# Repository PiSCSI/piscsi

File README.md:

# What is PiSCSI?

PiSCSI is a virtual SCSI device emulator that runs on a Raspberry Pi through the [PiSCSI hat](https://github.com/PiSCSI/piscsi/wiki/Hardware-Versions).
The software runs in userspace, and can emulate several SCSI devices at one time.
There is a control interface to attach / detach drives during runtime, as well as insert and eject removable media.

This project aims to be compliant with the SCSI specification and usable with any standards compliant SCSI controller (see [compatibility list](https://github.com/PiSCSI/piscsi/wiki/Compatibility)).
A handful of PiSCSI features were written specifically for vintage Macintosh and Atari computers and may depend on non-free device drivers on the host machine.

PiSCSI is a fork of [RaSCSI](https://github.com/RaSCSI/RaSCSI) and maintains compatibility with any RaSCSI hat.

Please check out the full story with much more detail on the [wiki](https://github.com/PiSCSI/piscsi/wiki)!

Browse the generated [PiSCSI command documentation](https://piscsi.github.io/piscsi/).

## How do I contribute?

PiSCSI is using a variant of the Gitflow Workflow. A quick overview:

- The *main* branch should always reflect the contents of the last stable release
- The *develop* branch should contain the latest tested & approved updates. Pull requests should be used to merge changes into develop.
- The rest of the feature branches are for developing new features
- A tag will be created for each "release". The releases will be named \<year\>.\<month\>.\<release number\> where the release number is incremented for each subsequent release tagged in the same calendar month. The first release of the month of January 2021 is called "21.01.01", the second one in the same month "21.01.02" and so on.

Note that the leading zeroes in the month and release number are used only in the git tags. The equivalent version number in the software is 21.1.1, 21.1.2, etc.

When you are ready to contribute code to PiSCSI, follow the [GitHub Forking and Pull Request workflow](https://docs.github.com/en/get-started/exploring-projects-on-github/contributing-to-a-project) to create your own fork where you can make changes, and then contribute it back to the project. Please remember to always make Pull Requests against the *develop* branch.

If you want to add a new translation, or improve upon an existing one, please follow the [Web Interface localization instructions](go/piscsi-web/README.md#updating-localizations). Once the translation is complete, please use the same workflow as above to contribute it to the project.

## GitHub Sponsors

Thank you to all of the GitHub sponsors who support the development community!

Extra special thank you to the Gold level sponsors!

- [@mikelord68](https://github.com/mikelord68)
- [@SamplerSpa-dev](https://github.com/SamplerSpa-de)

Special thank you to the Silver level sponsors!

- [@stinkerton18](https://github.com/stinkerton18)
- [@hsiboy](https://github.com/hsiboy)
- [@pendleton115](https://github.com/pendleton115)
- [@Teufelhunden-0311](https://github.com/Teufelhunden-0311)
- Private sponsor ;]

Thank you to Lin van der Slikke for the red panda logo design!

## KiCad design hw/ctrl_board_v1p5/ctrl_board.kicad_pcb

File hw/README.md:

# Where's the hardware?

The hardware design files have been moved to a separate repository at:
https://github.com/PiSCSI/piscsi-hw

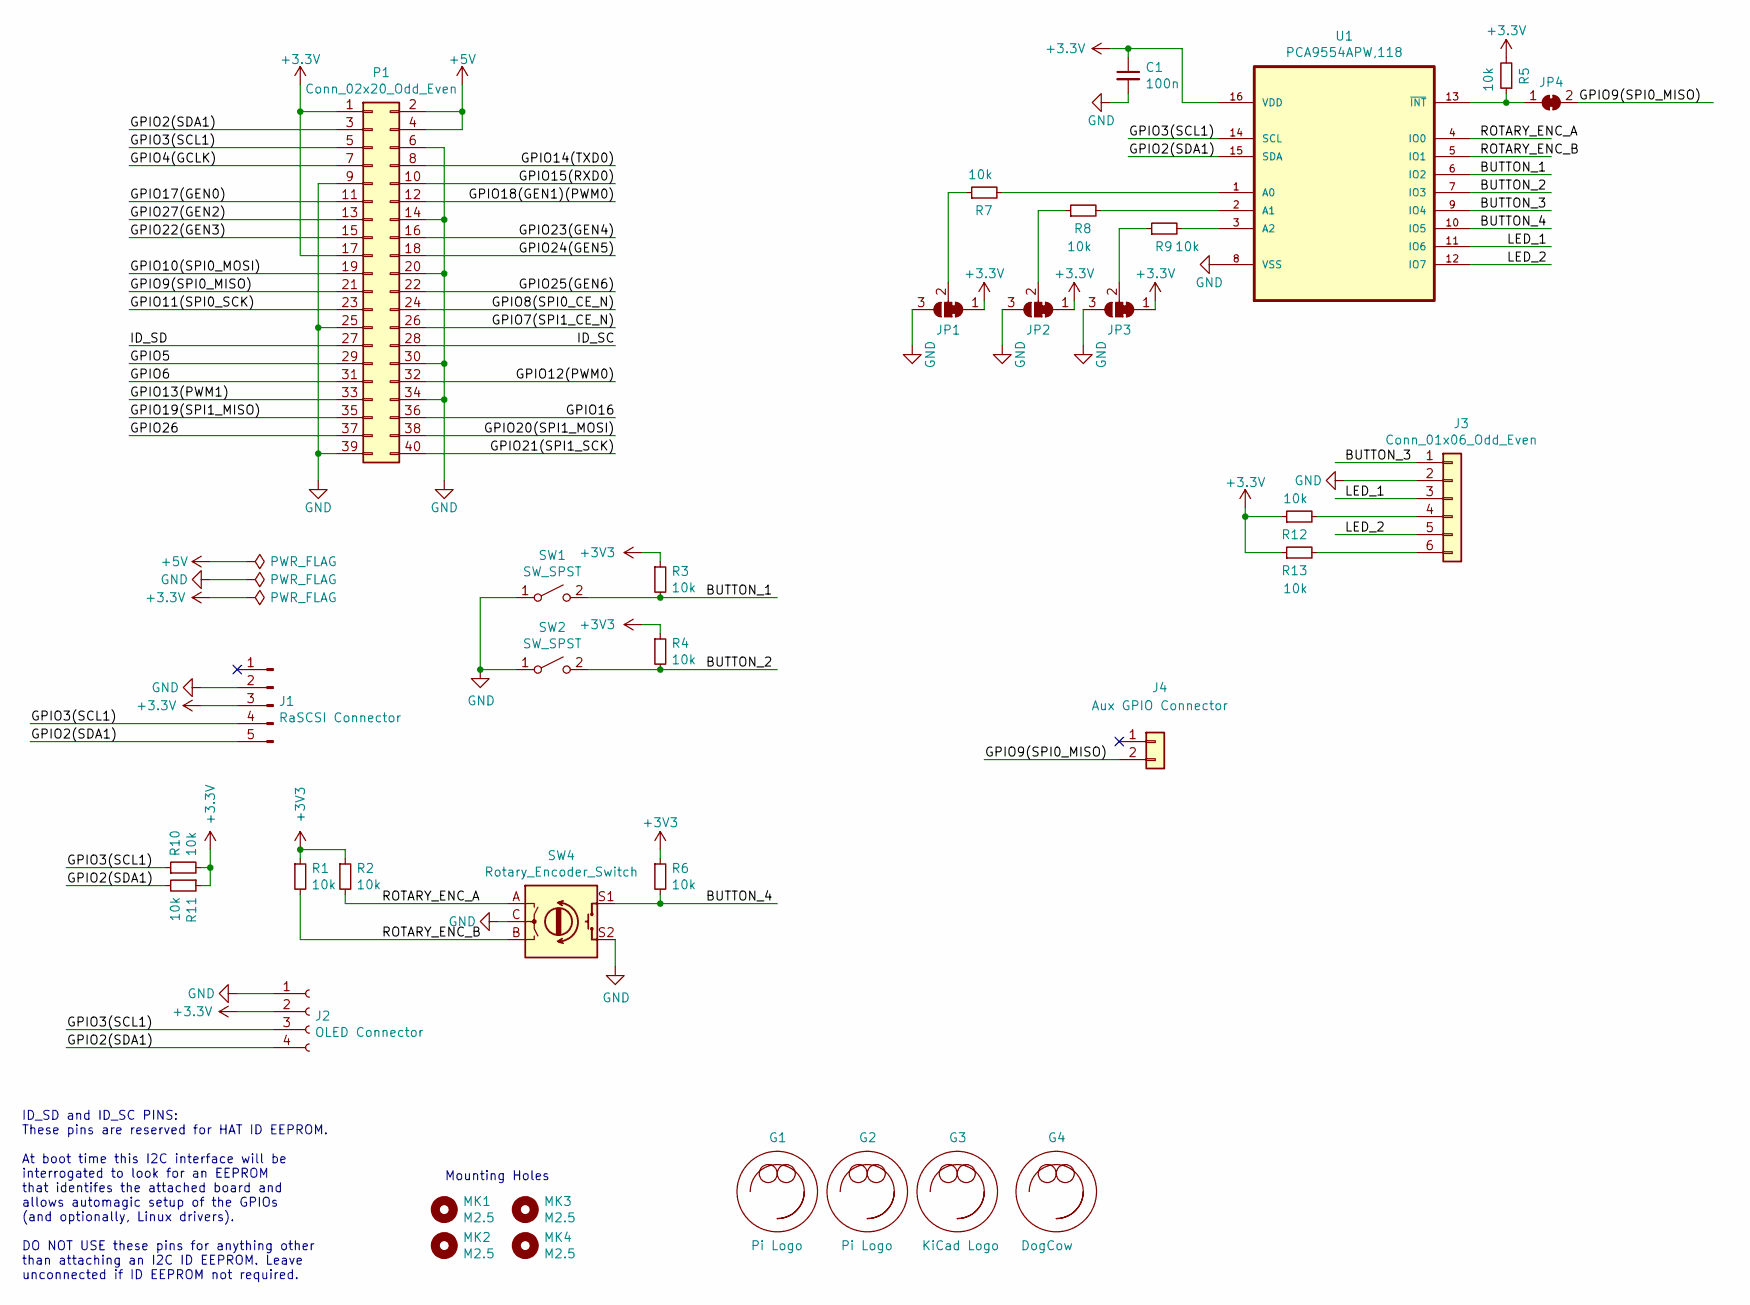
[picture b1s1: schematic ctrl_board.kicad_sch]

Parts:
C1: 100n; C_0805_2012Metric; LCSC C49678
G1, G2: Pi Logo; pi_logo
G3: KiCad Logo; KiCad-Logo2_5mm_SilkScreen
G4: DogCow; dogcow
J1: RaSCSI Connector; PinHeader_1x05_P2.54mm_Vertical
J2: OLED Connector; 0.9_and_1.3_in_OLED_Footprint
J3: Conn_01x06_Odd_Even; PinHeader_1x06_P2.54mm_Vertical
J4: Aux GPIO Connector; PinHeader_1x02_P2.54mm_Vertical
JP1, JP2, JP3: SolderJumper_3_Bridged12; SolderJumper-3_P1.3mm_Bridged12_RoundedPad1.0x1.5mm
JP4: SolderJumper_2_Open; SolderJumper-2_P1.3mm_Bridged_RoundedPad1.0x1.5mm
MK1, MK2, MK3, MK4: M2.5; MountingHole_2.7mm_M2.5
P1: Conn_02x20_Odd_Even; PinSocket_2x20_P2.54mm_Vertical
R1, R2, R3, R4, R5, R6, R7, R8, R9, R10, R11, R12, R13: 10k; R_0805_2012Metric; LCSC C17414
SW1, SW2: SW_SPST; SW_PUSH_6mm_H5mm; LCSC C110153
SW4: Rotary_Encoder_Switch; RotaryEncoder_Alps_EC11E-Switch_Vertical_H20mm
U1: PCA9554APW,118; TSSOP-16_4.4x5mm_P0.65mm; MPN PCA9554APW,118

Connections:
+5V: P1.2, P1.4
/BUTTON_1: R3.2, SW1.2 (B), U1.6 (IO2)
/BUTTON_2: R4.2, SW2.2 (B), U1.7 (IO3)
/BUTTON_3: J3.1, U1.9 (IO4)
/BUTTON_4: R6.2, SW4.S1, U1.10 (IO5)
/GPIO2(SDA1): J1.5, J2.4, P1.3, R11.2, U1.15 (SDA)
/GPIO3(SCL1): J1.4, J2.3, P1.5, R10.1, U1.14 (SCL)
/GPIO4(GCLK): P1.7
/GPIO5: P1.29
/GPIO6: P1.31
/GPIO7(SPI1_CE_N): P1.26
/GPIO8(SPI0_CE_N): P1.24
/GPIO9(SPI0_MISO): J4.2, JP4.2 (B), P1.21
/GPIO10(SPI0_MOSI): P1.19
/GPIO11(SPI0_SCK): P1.23
/GPIO12(PWM0): P1.32
/GPIO13(PWM1): P1.33
/GPIO14(TXD0): P1.8
/GPIO15(RXD0): P1.10
/GPIO16: P1.36
/GPIO17(GEN0): P1.11
/GPIO18(GEN1)(PWM0): P1.12
/GPIO19(SPI1_MISO): P1.35
/GPIO20(SPI1_MOSI): P1.38
/GPIO21(SPI1_SCK): P1.40
/GPIO22(GEN3): P1.15
/GPIO23(GEN4): P1.16
/GPIO24(GEN5): P1.18
/GPIO25(GEN6): P1.22
/GPIO26: P1.37
/GPIO27(GEN2): P1.13
/ID_SC: P1.28
/ID_SD: P1.27
/LED_1: J3.3, U1.11 (IO6)
/LED_2: J3.5, U1.12 (IO7)
/ROTARY_ENC_A: R2.2, SW4.A, U1.4 (IO0)
/ROTARY_ENC_B: R1.2, SW4.B, U1.5 (IO1)
GND: C1.2, J1.2, J2.1, J3.2, JP1.3 (B), JP2.3 (B), JP3.3 (B), P1.6, P1.9, P1.14, P1.20, P1.25, P1.30, P1.34, P1.39, SW1.1 (A), SW2.1 (A), SW4.C, SW4.S2, U1.8 (VSS)
unnamed: J3.4, R12.2
unnamed: J3.6, R13.2
unnamed: JP1.2 (C), R7.1
unnamed: JP2.2 (C), R8.1
unnamed: JP3.2 (C), R9.1
unnamed: JP4.1 (A), R5.1, U1.13 (~INT)
unnamed: R7.2, U1.1 (A0)
unnamed: R8.2, U1.2 (A1)
unnamed: R9.2, U1.3 (A2)

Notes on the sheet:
ID_SD and ID_SC PINS: These pins are reserved for HAT ID EEPROM. At boot time this I2C interface will be interrogated to look for an EEPROM that identifes the attached board and allows automagic setup of the GPIOs (and optionally, Linux drivers). DO NOT USE these pins for anything other than attach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
Mounting Holes

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
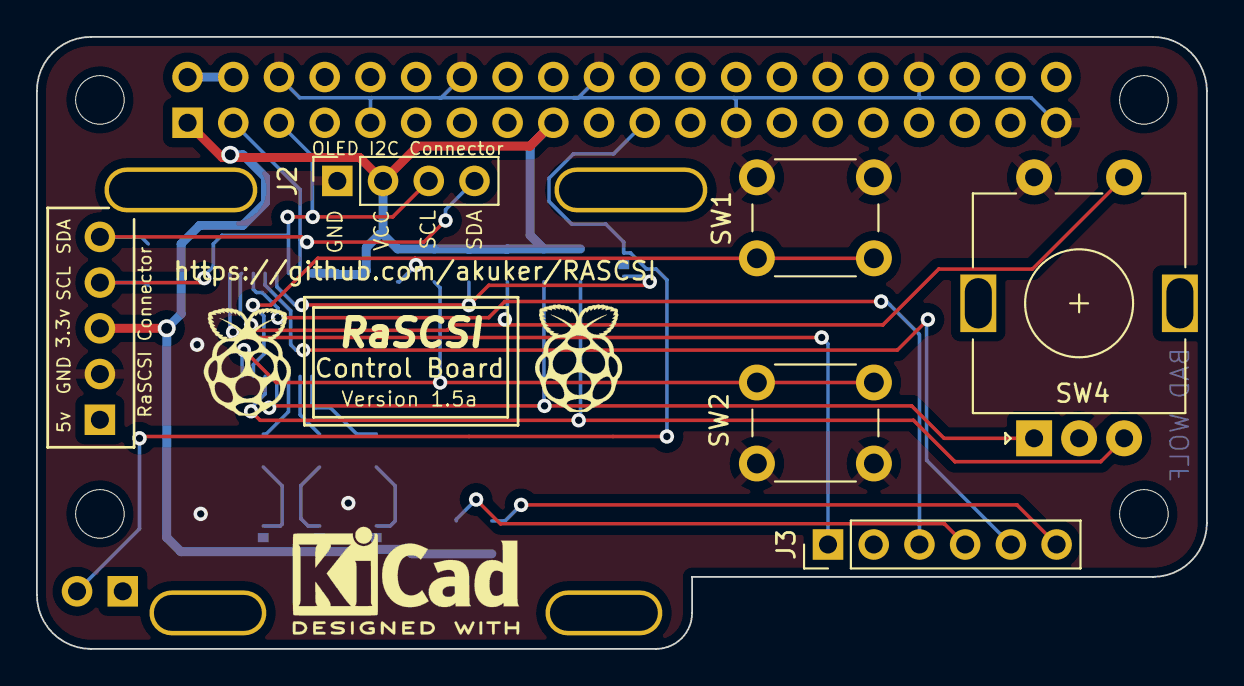
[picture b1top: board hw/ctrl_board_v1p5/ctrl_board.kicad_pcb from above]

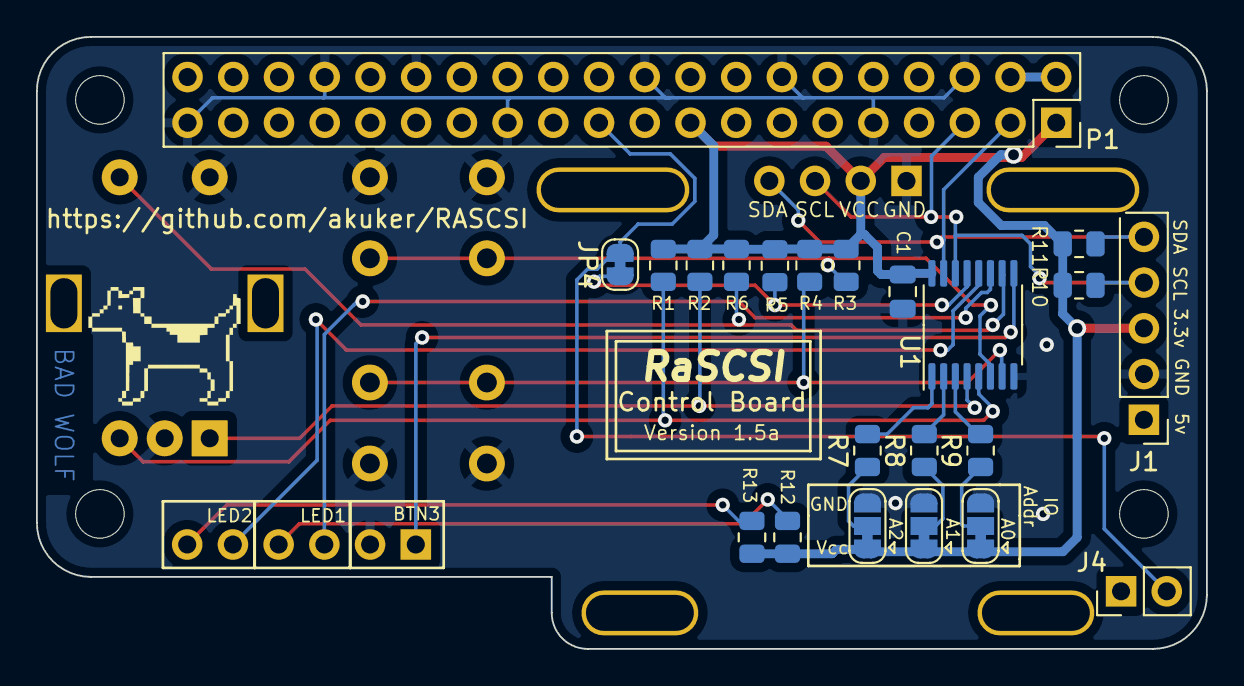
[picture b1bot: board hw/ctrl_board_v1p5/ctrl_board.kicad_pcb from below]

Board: 2 copper layers, 65.0 x 34.0 mm, 35 parts (26 on the bottom side), 23 nets.

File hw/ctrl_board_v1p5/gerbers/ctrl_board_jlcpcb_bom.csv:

Comment,Designator,Footprint,LCSC
"100n","C1","Capacitor_SMD:C_0805_2012Metric","C49678"
"RaSCSI Connector","J1","Connector_PinHeader_2.54mm:PinHeader_1x05_P2.54mm_Vertical",""
"OLED Connector","J2","mousebites:0.9_and_1.3_in_OLED_Footprint",""
"Conn_01x06_Odd_Even","J3","Connector_PinHeader_2.54mm:PinHeader_1x06_P2.54mm_Vertical",""
"Aux GPIO Connector","J4","Connector_PinHeader_2.54mm:PinHeader_1x02_P2.54mm_Vertical",""
"SolderJumper_3_Bridged12","JP1,JP2,JP3","Jumper:SolderJumper-3_P1.3mm_Bridged12_RoundedPad1.0x1.5mm",""
"SolderJumper_2_Open","JP4","Jumper:SolderJumper-2_P1.3mm_Bridged_RoundedPad1.0x1.5mm",""
"M2.5","MK1,MK2,MK3,MK4","MountingHole:MountingHole_2.7mm_M2.5",""
"Conn_02x20_Odd_Even","P1","Connector_PinSocket_2.54mm:PinSocket_2x20_P2.54mm_Vertical",""
"10k","R1,R2,R3,R4,R5,R6,R7,R8,R9,R10,R11,R12,R13","Resistor_SMD:R_0805_2012Metric","C17414"
"SW_SPST","SW1,SW2","Button_Switch_THT:SW_PUSH_6mm_H5mm","C110153"
"Rotary_Encoder_Switch","SW4","Rotary_Encoder:RotaryEncoder_Alps_EC11E-Switch_Vertical_H20mm",""
"PCA9554APW,118","U1","Package_SO:TSSOP-16_4.4x5mm_P0.65mm","C86803"

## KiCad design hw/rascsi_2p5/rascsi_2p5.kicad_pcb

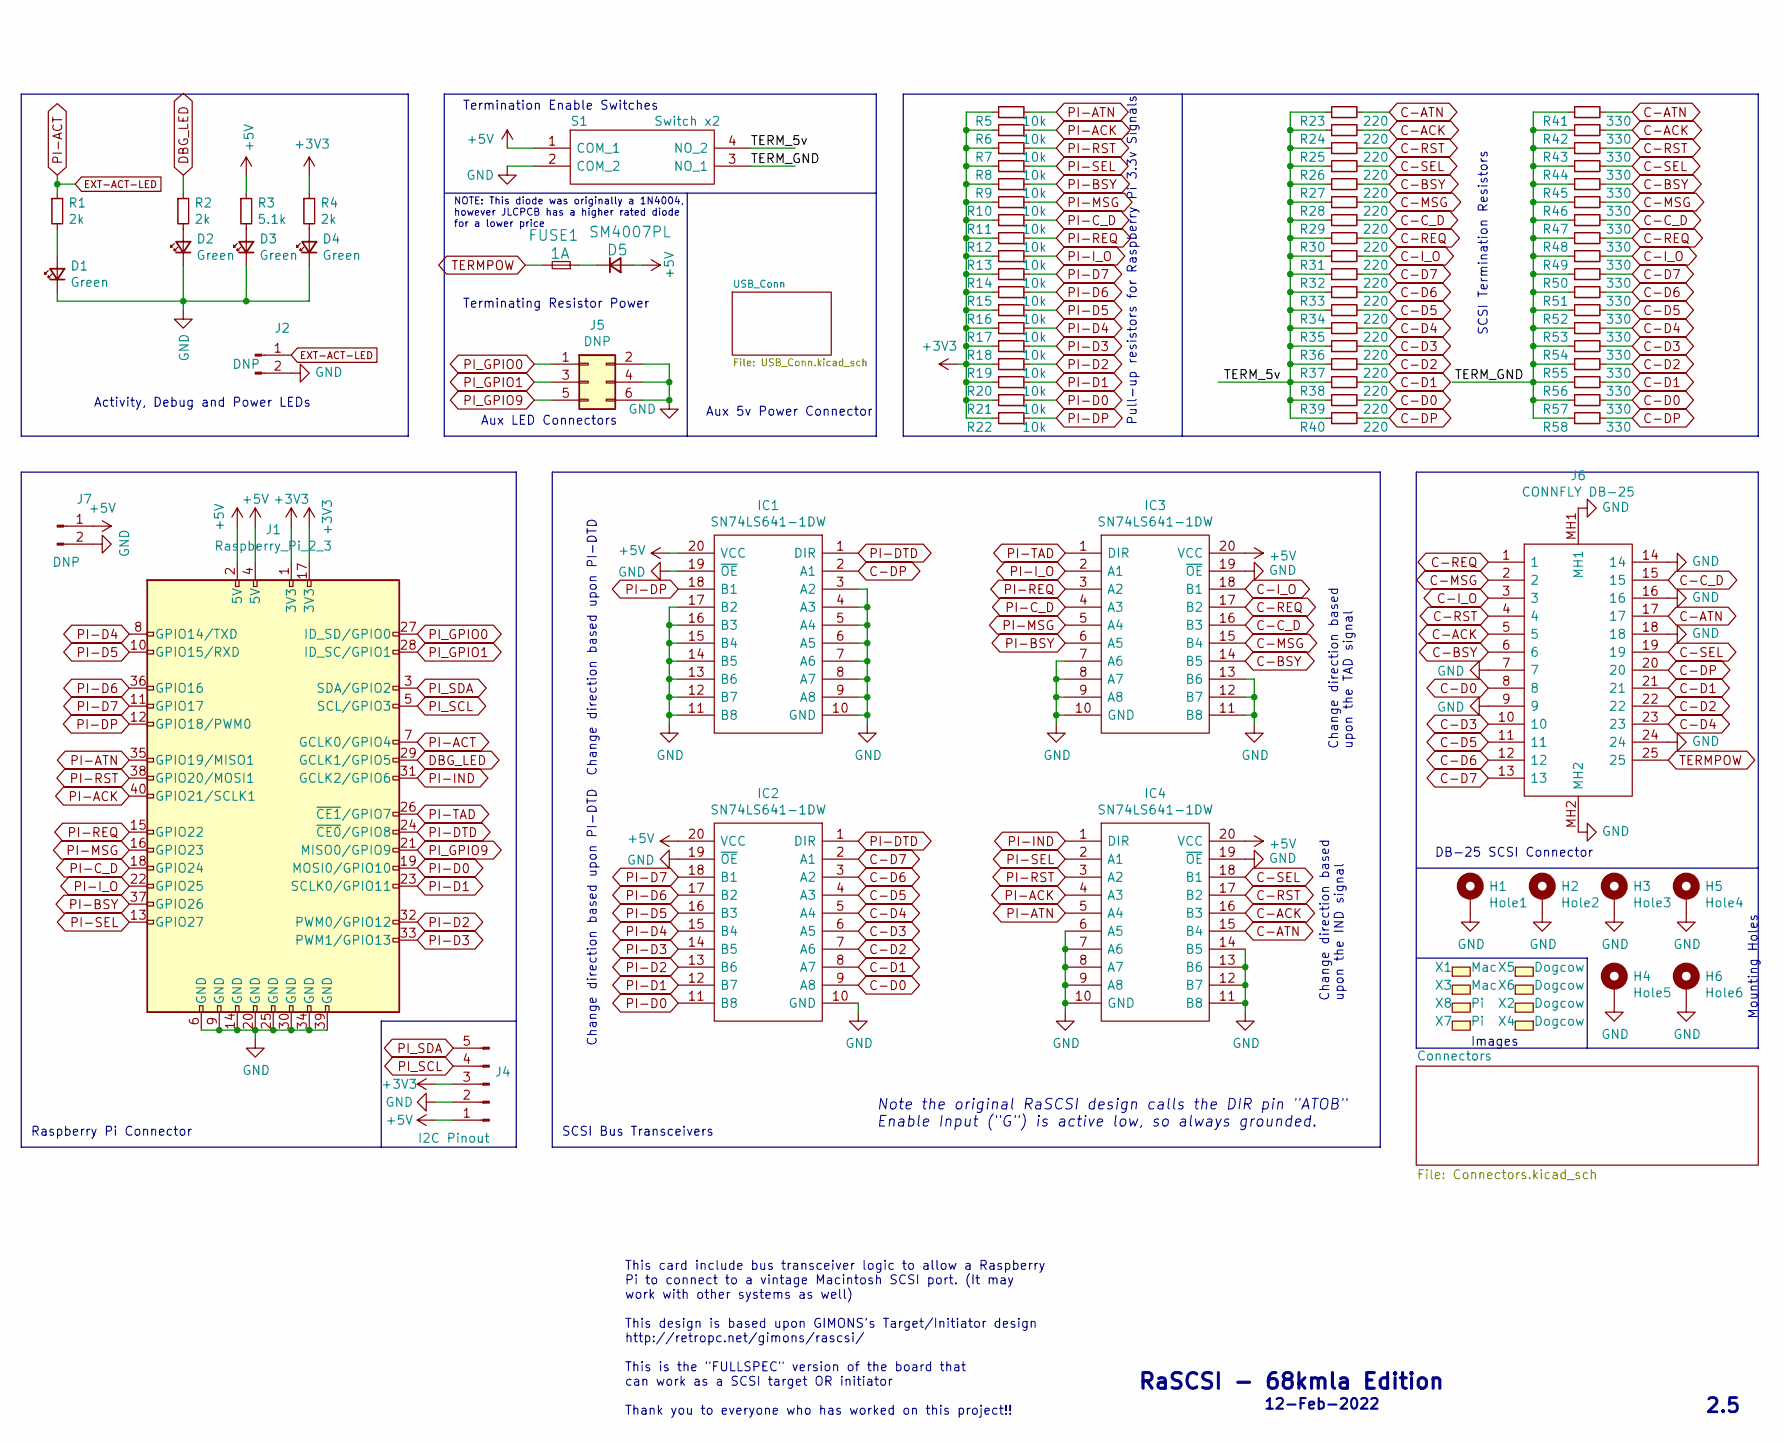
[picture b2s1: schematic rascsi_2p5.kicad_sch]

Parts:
D1, D2, D3, D4: Green; LED_0805_2012Metric; Manufacturer_Part_Number C2297; LCSC C2297
D5: SM4007PL; D_SOD-123F; Manufacturer_Part_Number SM4007PL; LCSC C64898
FUSE1: 1A; Fuse_1206_3216Metric; Manufacturer_Part_Number 12B1100B; LCSC C182974
H1: Hole1; MountingHole_2.7mm_M2.5_Pad_Via; Manufacturer_Part_Number DNP; LCSC DNP
H2: Hole2; MountingHole_2.7mm_M2.5_Pad_Via; Manufacturer_Part_Number DNP; LCSC DNP
H3: Hole3; MountingHole_2.7mm_M2.5_Pad_Via; Manufacturer_Part_Number DNP; LCSC DNP
H4: Hole5; MountingHole_2.7mm_M2.5_Pad_Via; Manufacturer_Part_Number DNP; LCSC DNP
H5: Hole4; MountingHole_2.7mm_M2.5_Pad_Via; Manufacturer_Part_Number DNP; LCSC DNP
H6: Hole6; MountingHole_2.7mm_M2.5_Pad_Via; Manufacturer_Part_Number DNP; LCSC DNP
IC1, IC2, IC3, IC4: SN74LS641-1DW; SOIC127P1030X265-20N; Manufacturer_Part_Number SN74LS641-1DW; LCSC N/A
J1: Raspberry_Pi_2_3; PinSocket_2x20_P2.54mm_Vertical; Manufacturer_Part_Number C50982; LCSC C50982
J2: DNP; PinHeader_1x02_P2.54mm_Horizontal; Manufacturer_Part_Number DNP; LCSC DNP
J4: I2C Pinout; PinSocket_1x05_P2.54mm_Vertical; Manufacturer_Part_Number C50950; LCSC C50950
J5: DNP; PinHeader_2x03_P2.54mm_Vertical; Manufacturer_Part_Number DNP; LCSC DNP
J6: CONNFLY DB-25; L717SDB25PA4CH4F; Manufacturer_Part_Number DS1037-25FNAKT74-0CC; LCSC C77838
J7: DNP; PinHeader_1x02_P2.54mm_Vertical; Manufacturer_Part_Number DNP; LCSC DNP
R1, R2, R4: 2k; R_0402_1005Metric; Manufacturer_Part_Number 0402WGF2001TCE; LCSC C4109
R3: 5.1k; R_0402_1005Metric; Manufacturer_Part_Number 0402WGF5101TCE; LCSC C25905
R5, R6, R7, R8, R9, R10, R11, R12, R13, R14, R15, R16, R17, R18, R19, R20, R21, R22: 10k; R_0402_1005Metric; Manufacturer_Part_Number 0402WGF1002TCE; LCSC C25744
R23, R24, R25, R26, R27, R28, R29, R30, R31, R32, R33, R34, R35, R36, R37, R38, R39, R40: 220; R_0402_1005Metric; Manufacturer_Part_Number 0402WGF2200TCE; LCSC C25091
R41, R42, R43, R44, R45, R46, R47, R48, R49, R50, R51, R52, R53, R54, R55, R56, R57, R58: 330; R_0402_1005Metric; Manufacturer_Part_Number 0402WGF3300TCE; LCSC C25104
S1: Switch x2; SOIC127P812X230-4N; Manufacturer_Part_Number DSHP02TSGET; LCSC C40735
X1, X3: Mac; mac_happy_small; Manufacturer_Part_Number N/A; LCSC N/A
X2, X4, X5, X6: Dogcow; dogcow; Manufacturer_Part_Number N/A; LCSC N/A
X7: Pi; pi_logo; Manufacturer_Part_Number N/A; LCSC N/A
X8: Pi; scsi_logo; Manufacturer_Part_Number N/A; LCSC N/A

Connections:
+3V3: J1.1 (3V3), J1.17 (3V3), J4.3, R4.1, R5.1, R6.1, R7.1, R8.1, R9.1, R10.1, R11.1, R12.1, R13.1, R14.1, R15.1, R16.1, R17.1, R18.1, R19.1, R20.1, R21.1, R22.1
+5V: D5.2 (A), IC1.20 (VCC), IC2.20 (VCC), IC3.20 (VCC), IC4.20 (VCC), J1.2 (5V), J1.4 (5V), J4.1, J7.1, R3.1, S1.1 (COM_1); also elsewhere on the board
/TERM_5v: R23.1, R24.1, R25.1, R26.1, R27.1, R28.1, R29.1, R30.1, R31.1, R32.1, R33.1, R34.1, R35.1, R36.1, R37.1, R38.1, R39.1, R40.1, S1.4 (NO_2)
/TERM_GND: R41.1, R42.1, R43.1, R44.1, R45.1, R46.1, R47.1, R48.1, R49.1, R50.1, R51.1, R52.1, R53.1, R54.1, R55.1, R56.1, R57.1, R58.1, S1.3 (NO_1)
C-ACK: IC4.16 (B3), J6.5, R24.2, R42.2; also elsewhere on the board
C-ATN: IC4.15 (B4), J6.17, R23.2, R41.2; also elsewhere on the board
C-BSY: IC3.14 (B5), J6.6, R27.2, R45.2; also elsewhere on the board
C-C_D: IC3.16 (B3), J6.15, R29.2, R47.2; also elsewhere on the board
C-D0: IC2.9 (A8), J6.8, R39.2, R57.2; also elsewhere on the board
C-D1: IC2.8 (A7), J6.21, R38.2, R56.2; also elsewhere on the board
C-D2: IC2.7 (A6), J6.22, R37.2, R55.2; also elsewhere on the board
C-D3: IC2.6 (A5), J6.10, R36.2, R54.2; also elsewhere on the board
C-D4: IC2.5 (A4), J6.23, R35.2, R53.2; also elsewhere on the board
C-D5: IC2.4 (A3), J6.11, R34.2, R52.2; also elsewhere on the board
C-D6: IC2.3 (A2), J6.12, R33.2, R51.2; also elsewhere on the board
C-D7: IC2.2 (A1), J6.13, R32.2, R50.2; also elsewhere on the board
C-DP: IC1.2 (A1), J6.20, R40.2, R58.2; also elsewhere on the board
C-I_O: IC3.18 (B1), J6.3, R31.2, R49.2; also elsewhere on the board
C-MSG: IC3.15 (B4), J6.2, R28.2, R46.2; also elsewhere on the board
C-REQ: IC3.17 (B2), J6.1, R30.2, R48.2; also elsewhere on the board
C-RST: IC4.17 (B2), J6.4, R25.2, R43.2; also elsewhere on the board
C-SEL: IC4.18 (B1), J6.19, R26.2, R44.2; also elsewhere on the board
DBG_LED: J1.29 (GCLK1/GPIO5), R2.1
GND: D1.1 (K), D2.1 (K), D3.1 (K), D4.1 (K), H1.1, H2.1, H3.1, H4.1, H5.1, H6.1, IC1.3 (A2), IC1.4 (A3), IC1.5 (A4), IC1.6 (A5), IC1.7 (A6), IC1.8 (A7), IC1.9 (A8), IC1.10 (GND), IC1.11 (B8), IC1.12 (B7), IC1.13 (B6), IC1.14 (B5), IC1.15 (B4), IC1.16 (B3), IC1.17 (B2), IC1.19 (~OE), IC2.10 (GND), IC2.19 (~OE), IC3.7 (A6), IC3.8 (A7), IC3.9 (A8), IC3.10 (GND), IC3.11 (B8), IC3.12 (B7), IC3.13 (B6), IC3.19 (~OE), IC4.6 (A5), IC4.7 (A6), IC4.8 (A7), IC4.9 (A8), IC4.10 (GND), IC4.11 (B8), IC4.12 (B7), IC4.13 (B6), IC4.14 (B5), IC4.19 (~OE), J1.6 (GND), J1.9 (GND), J1.14 (GND), J1.20 (GND), J1.25 (GND), J1.30 (GND), J1.34 (GND), J1.39 (GND), J2.2, J4.2, J5.2, J5.4, J5.6, J6.7, J6.9, J6.14, J6.16, J6.18, J6.24, J6.MH1, J6.MH2, J7.2, S1.2 (COM_2); also elsewhere on the board
unnamed: D1.2 (A), R1.2
unnamed: D2.2 (A), R2.2
unnamed: D3.2 (A), R3.2
unnamed: D4.2 (A), R4.2
unnamed: D5.1 (K), FUSE1.1
PB_LED_Pin: J1.7 (GCLK0/GPIO4), J2.1, R1.1; also elsewhere on the board
PI-ACK: IC4.4 (A3), J1.40 (GPIO21/SCLK1), R6.2
PI-ATN: IC4.5 (A4), J1.35 (GPIO19/MISO1), R5.2
PI-BSY: IC3.6 (A5), J1.37 (GPIO26), R9.2
PI-C_D: IC3.4 (A3), J1.18 (GPIO24), R11.2
PI-D0: IC2.11 (B8), J1.19 (MOSI0/GPIO10), R21.2
PI-D1: IC2.12 (B7), J1.23 (SCLK0/GPIO11), R20.2
PI-D2: IC2.13 (B6), J1.32 (PWM0/GPIO12), R19.2
PI-D3: IC2.14 (B5), J1.33 (PWM1/GPIO13), R18.2
PI-D4: IC2.15 (B4), J1.8 (GPIO14/TXD), R17.2
PI-D5: IC2.16 (B3), J1.10 (GPIO15/RXD), R16.2
PI-D6: IC2.17 (B2), J1.36 (GPIO16), R15.2
PI-D7: IC2.18 (B1), J1.11 (GPIO17), R14.2
PI-DP: IC1.18 (B1), J1.12 (GPIO18/PWM0), R22.2
PI-DTD: IC1.1 (DIR), IC2.1 (DIR), J1.24 (~CE0/GPIO8)
PI-IND: IC4.1 (DIR), J1.31 (GCLK2/GPIO6)
PI-I_O: IC3.2 (A1), J1.22 (GPIO25), R13.2
PI-MSG: IC3.5 (A4), J1.16 (GPIO23), R10.2
PI-REQ: IC3.3 (A2), J1.15 (GPIO22), R12.2
PI-RST: IC4.3 (A2), J1.38 (GPIO20/MOSI1), R7.2
PI-SEL: IC4.2 (A1), J1.13 (GPIO27), R8.2
PI-TAD: IC3.1 (DIR), J1.26 (~CE1/GPIO7)
PI_GPIO0: J1.27 (ID_SD/GPIO0), J5.1
PI_GPIO1: J1.28 (ID_SC/GPIO1), J5.3
PI_GPIO9: J1.21 (MISO0/GPIO9), J5.5
PI_SCL: J1.5 (SCL/GPIO3), J4.4
PI_SDA: J1.3 (SDA/GPIO2), J4.5
TERMPOW: FUSE1.2, J6.25; also elsewhere on the board

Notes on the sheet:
Images
RaSCSI - 68kmla Edition
2.5
Raspberry Pi Connector
Change direction based upon the TAD signal
Terminating Resistor Power
Mounting Holes
12-Feb-2022
DB-25 SCSI Connector
SCSI Termination Resistors
Pull-up resistors for Raspberry Pi 3.3v Signals
Change direction based upon the IND signal
NOTE: This diode was originally a 1N4004, however JLCPCB has a higher rated diode for a lower price
Change direction based upon PI-DTD
Note the original RaSCSI design calls the DIR pin "ATOB" Enable Input ("G") is active low, so always grounded.
Activity, Debug and Power LEDs
Termination Enable Switches
This card include bus transceiver logic to allow a Raspberry Pi to connect to a vintage Macintosh SCSI port. (It may work with other systems as well) This design is based upon GIMONS's Target/Initiator design http://retropc.net/gimons/rascsi/ This is the "FULLSPEC" version of the board that can wor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
Aux 5v Power Connector
SCSI Bus Transceivers
Aux LED Connectors

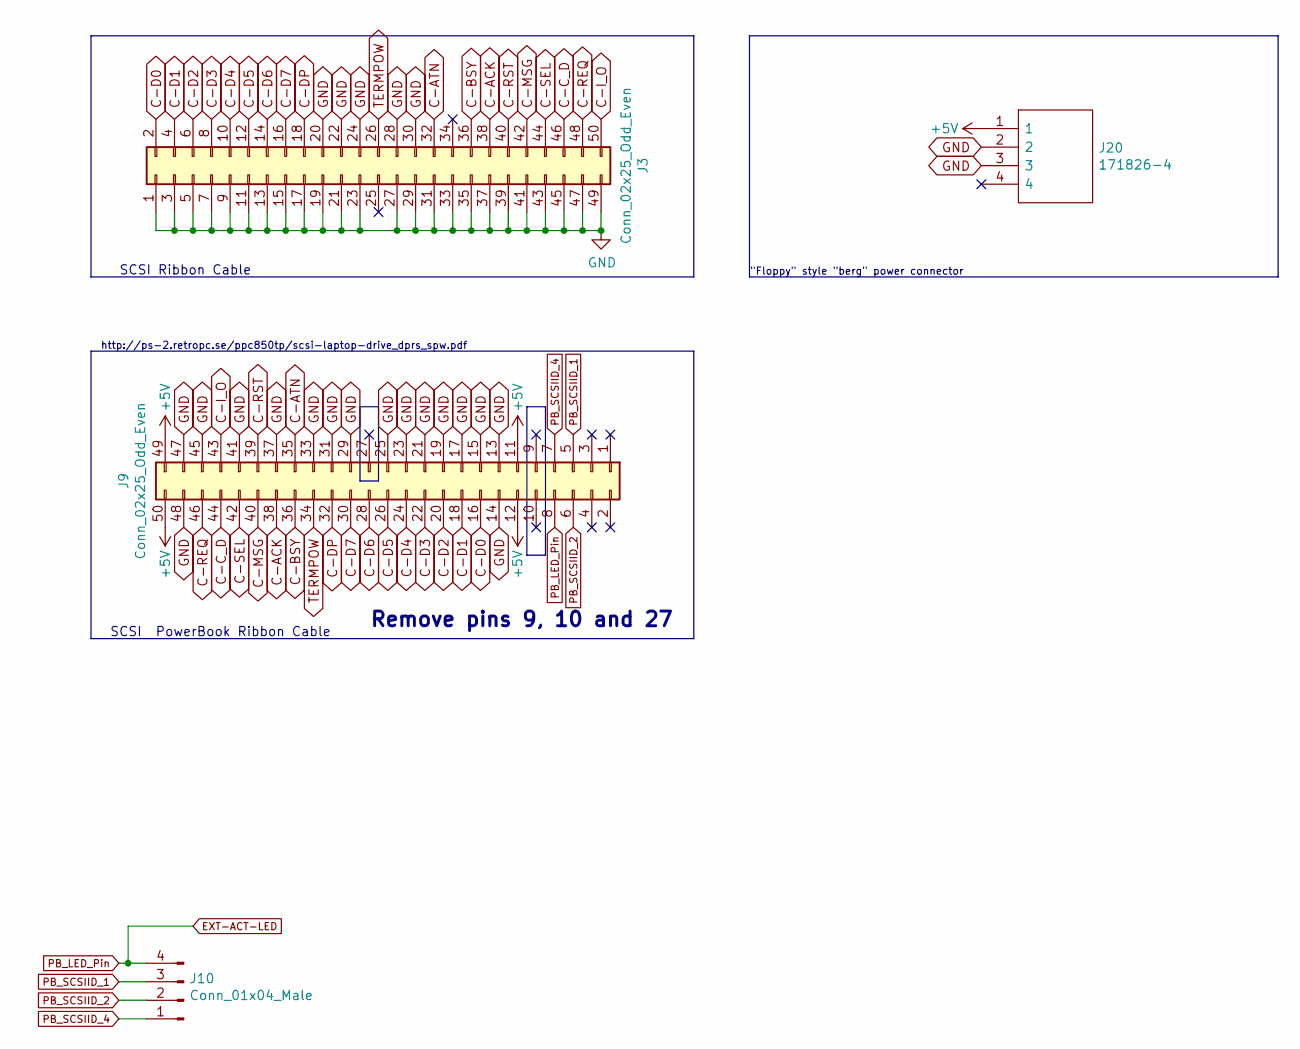
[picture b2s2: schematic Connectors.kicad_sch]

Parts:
J3: Conn_02x25_Odd_Even; PinHeader_2x25_P2.54mm_Vertical; Manufacturer_Part_Number C30006; LCSC C30006
J9: Conn_02x25_Odd_Even; PinHeader_2x25_P2.00mm_Horizontal; Manufacturer_Part_Number C3407; LCSC C3407
J10: Conn_01x04_Male; PinHeader_1x04_P2.00mm_Vertical
J20: 171826-4; SHDRRA4W69P0X250_1X4_1000X1350X670P; Mouser Part Number 571-1718264

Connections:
+5V: J9.11, J9.12, J9.49, J9.50, J20.1; also elsewhere on the board
C-ACK: J3.38, J9.38; also elsewhere on the board
C-ATN: J3.32, J9.35; also elsewhere on the board
C-BSY: J3.36, J9.36; also elsewhere on the board
C-C_D: J3.46, J9.44; also elsewhere on the board
C-D0: J3.2, J9.16; also elsewhere on the board
C-D1: J3.4, J9.18; also elsewhere on the board
C-D2: J3.6, J9.20; also elsewhere on the board
C-D3: J3.8, J9.22; also elsewhere on the board
C-D4: J3.10, J9.24; also elsewhere on the board
C-D5: J3.12, J9.26; also elsewhere on the board
C-D6: J3.14, J9.28; also elsewhere on the board
C-D7: J3.16, J9.30; also elsewhere on the board
C-DP: J3.18, J9.32; also elsewhere on the board
C-I_O: J3.50, J9.43; also elsewhere on the board
C-MSG: J3.42, J9.40; also elsewhere on the board
C-REQ: J3.48, J9.46; also elsewhere on the board
C-RST: J3.40, J9.39; also elsewhere on the board
C-SEL: J3.44, J9.42; also elsewhere on the board
GND: J3.1, J3.3, J3.5, J3.7, J3.9, J3.11, J3.13, J3.15, J3.17, J3.19, J3.20, J3.21, J3.22, J3.23, J3.24, J3.27, J3.28, J3.29, J3.30, J3.31, J3.33, J3.35, J3.37, J3.39, J3.41, J3.43, J3.45, J3.47, J3.49, J9.13, J9.14, J9.15, J9.17, J9.19, J9.21, J9.23, J9.25, J9.29, J9.31, J9.33, J9.37, J9.41, J9.45, J9.47, J9.48, J20.2, J20.3; also elsewhere on the board
PB_LED_Pin: J9.8, J10.4; also elsewhere on the board
PB_SCSIID_1: J9.5, J10.3
PB_SCSIID_2: J9.6, J10.2
PB_SCSIID_4: J9.7, J10.1
TERMPOW: J3.26, J9.34; also elsewhere on the board

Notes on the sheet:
Remove pins 9, 10 and 27
SCSI Ribbon Cable
"Floppy" style "berg" power connector
http://ps-2.retropc.se/ppc850tp/scsi-laptop-drive_dprs_spw.pdf
SCSI PowerBook Ribbon Cable

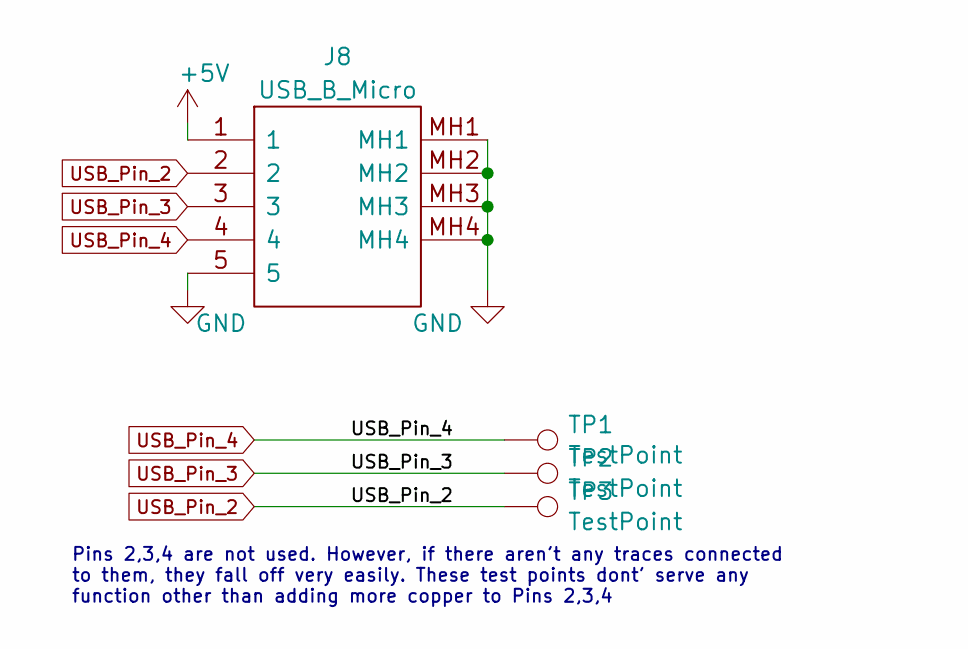
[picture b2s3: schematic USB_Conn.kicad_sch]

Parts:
J8: USB_B_Micro; U254051N4BH806; Manufacturer_Part_Number U254-051N-4BH806; LCSC C319170
TP1, TP2, TP3: TestPoint; TestPoint_Pad_D1.0mm; Manufacturer_Part_Number N/A; LCSC N/A

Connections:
+5V: J8.1; also elsewhere on the board
GND: J8.5, J8.MH1, J8.MH2, J8.MH3, J8.MH4; also elsewhere on the board
USB_Pin_2: J8.2, TP3.1
USB_Pin_3: J8.3, TP2.1
USB_Pin_4: J8.4, TP1.1

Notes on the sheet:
Pins 2,3,4 are not used. However, if there aren't any traces connected to them, they fall off very easily. These test points dont' serve any function other than adding more copper to Pins 2,3,4

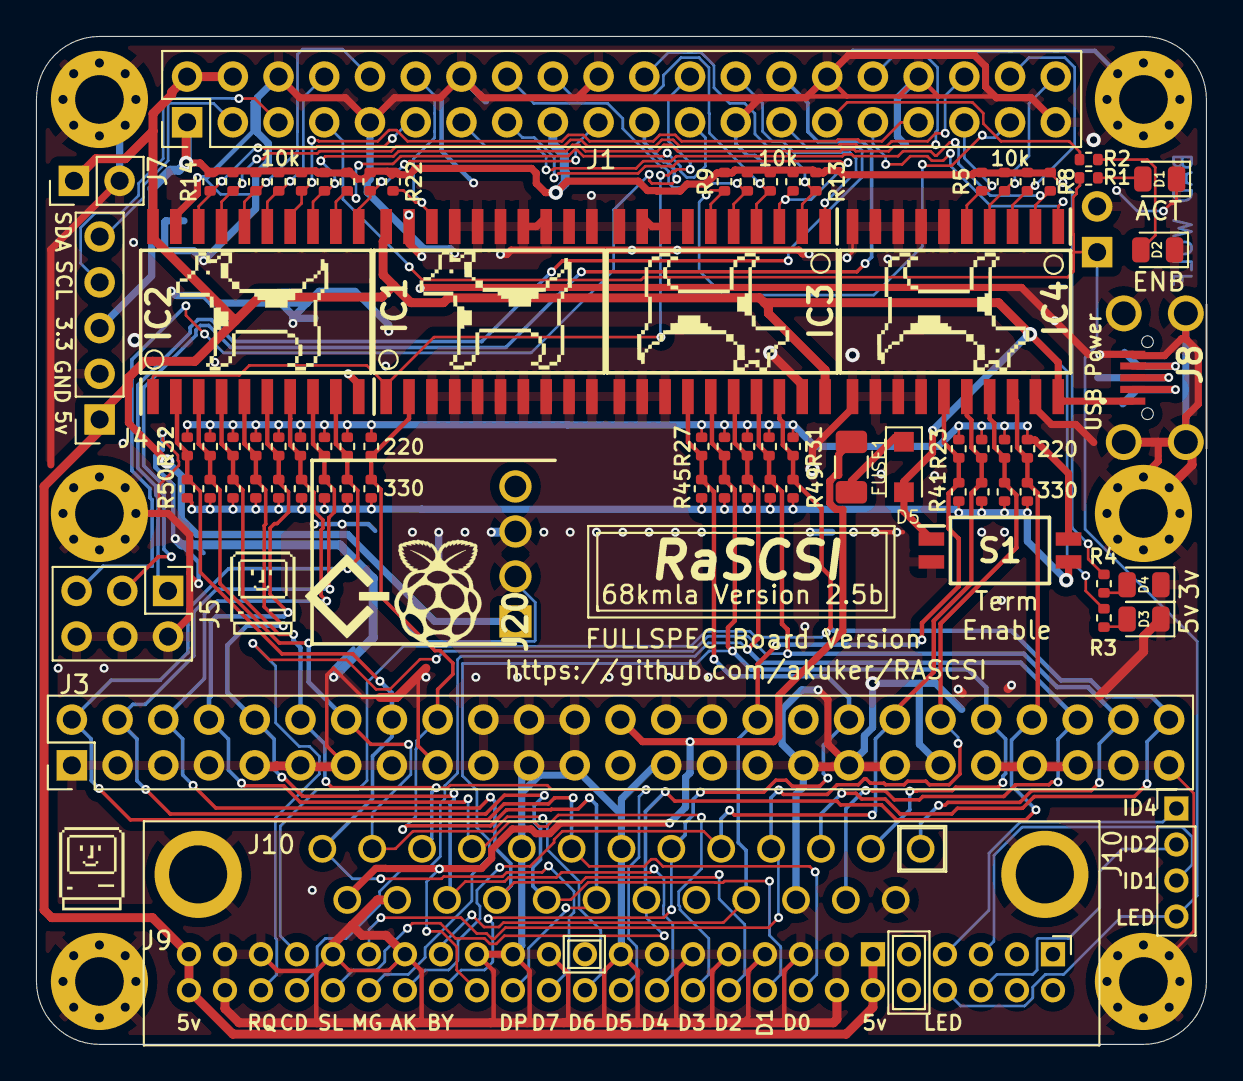
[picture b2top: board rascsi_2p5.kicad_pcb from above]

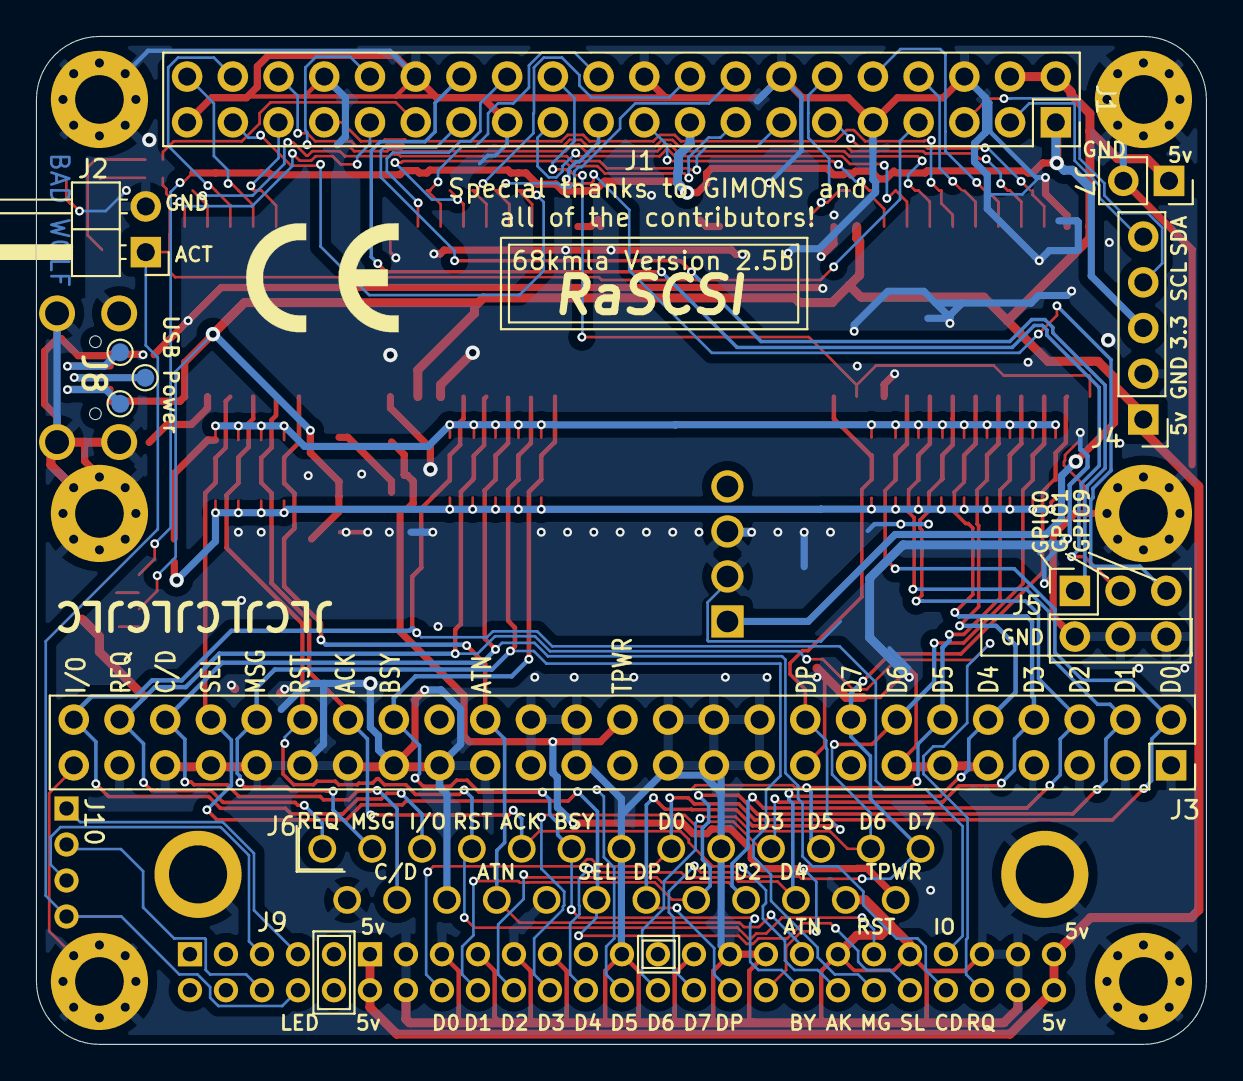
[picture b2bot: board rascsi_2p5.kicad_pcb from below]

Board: 2 copper layers, 65.0 x 56.0 mm, 97 parts (6 on the bottom side), 63 nets.

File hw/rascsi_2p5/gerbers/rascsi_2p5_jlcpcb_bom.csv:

Comment,Designator,Footprint,LCSC
Green,"D1,D2,D3,D4",LED_SMD:LED_0805_2012Metric,C2297
SM4007PL,D5,Diode_SMD:D_SOD-123F,C64898
1A,FUSE1,Fuse:Fuse_1206_3216Metric,C182974
Hole1,H1,MountingHole:MountingHole_2.7mm_M2.5_Pad_Via,DNP
Hole2,H2,MountingHole:MountingHole_2.7mm_M2.5_Pad_Via,DNP
Hole3,H3,MountingHole:MountingHole_2.7mm_M2.5_Pad_Via,DNP
Hole5,H4,MountingHole:MountingHole_2.7mm_M2.5_Pad_Via,DNP
Hole4,H5,MountingHole:MountingHole_2.7mm_M2.5_Pad_Via,DNP
Hole6,H6,MountingHole:MountingHole_2.7mm_M2.5_Pad_Via,DNP
SN74LS641-1DW,"IC1,IC2,IC3,IC4",SamacSys_Parts:SOIC127P1030X265-20N,N/A
Raspberry_Pi_2_3,J1,Connector_PinSocket_2.54mm:PinSocket_2x20_P2.54mm_Vertical,DNP
Conn_01x04_Male,J10,Connector_PinHeader_2.00mm:PinHeader_1x04_P2.00mm_Vertical,DNP
DNP,J2,Connector_PinHeader_2.54mm:PinHeader_1x02_P2.54mm_Horizontal,DNP
171826-4,J20,SHDRRA4W69P0X250_1X4_1000X1350X670P,DNP
Conn_02x25_Odd_Even,J3,Connector_PinHeader_2.54mm:PinHeader_2x25_P2.54mm_Vertical,DNP
I2C Pinout,J4,Connector_PinSocket_2.54mm:PinSocket_1x05_P2.54mm_Vertical,DNP
DNP,J5,Connector_PinHeader_2.54mm:PinHeader_2x03_P2.54mm_Vertical,DNP
CONNFLY DB-25,J6,SamacSys_Parts:L717SDB25PA4CH4F,DNP
DNP,J7,Connector_PinHeader_2.54mm:PinHeader_1x02_P2.54mm_Vertical,DNP
USB_B_Micro,J8,SamacSys_Parts:U254051N4BH806,C319170
Conn_02x25_Odd_Even,J9,Connector_PinHeader_2.00mm:PinHeader_2x25_P2.00mm_Horizontal,DNP
2k,"R1,R2,R4",Resistor_SMD:R_0402_1005Metric,C4109
220,"R23,R24,R25,R26,R27,R28,R29,R30,R31,R32,R33,R34,R35,R36,R37,R38,R39,R40",Resistor_SMD:R_0402_1005Metric,C25091
5.1k,R3,Resistor_SMD:R_0402_1005Metric,C25905
330,"R41,R42,R43,R44,R45,R46,R47,R48,R49,R50,R51,R52,R53,R54,R55,R56,R57,R58",Resistor_SMD:R_0402_1005Metric,C25104
10k,"R5,R6,R7,R8,R9,R10,R11,R12,R13,R14,R15,R16,R17,R18,R19,R20,R21,R22",Resistor_SMD:R_0402_1005Metric,C25744
Switch x2,S1,rascsi_din:SOIC127P812X230-4N,C40735
TestPoint,"TP1,TP2,TP3",TestPoint:TestPoint_Pad_D1.0mm,N/A
Mac,"X1,X3",SamacSys_Parts:mac_happy_small,N/A
Dogcow,"X2,X4,X5,X6",SamacSys_Parts:dogcow,N/A
Pi,X7,SamacSys_Parts:pi_logo,N/A
Pi,X8,SamacSys_Parts:scsi_logo,N/A

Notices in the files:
README.md:
License: BSD 3-Clause
